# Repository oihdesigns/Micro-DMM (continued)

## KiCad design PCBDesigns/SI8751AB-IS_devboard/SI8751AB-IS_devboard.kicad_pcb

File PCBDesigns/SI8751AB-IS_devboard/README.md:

# Si8751 AC/DC development board — revision C

KiCad 10 bench prototype targeting **120 V RMS AC / 170 V DC, less than 1 A**, initially with resistive loads. Two SI8751AB-IS drivers operate back-to-back STP12N60M2 MOSFETs. **AMC3330DWER** measures switched voltage with integrated isolated power; **ACS725LLCTR-05AB-T** measures bidirectional load current. The entire board uses one regulated 3.3 V input. All resistors and capacitors are **0805**. The board is two layers, 110 × 90 mm, for 1.6 mm FR-4 and 35 µm copper.

Open `SI8751AB-IS_devboard.kicad_pro`. Reload schematic and board if an earlier revision is still open. Local symbols and footprints, a schematic PDF, BOM, and validation reports/previews are included. Prototype Gerbers and drills are in `fabrication/revC/`. `revision_B_before_3V3_sensor.zip` preserves revision B; the earlier revision A backup is also retained. The inventory workbook was read without modification; existing project preferences were preserved.

## Changes from revision B

- Replaced ACS712-05B with **ACS725LLCTR-05AB-T**, powered from +3V3.
- Removed the 5 V net. J1-7 is **NC**, preserving all other revision B header pin numbers.
- Removed R15/R16, the 2:1 current-output divider. J1-8 now receives the sensor output directly.
- C17 remains 100 nF; the ACS725 internal filter resistance gives approximately 884 Hz bandwidth. C18 is a direct 1 nF output load.
- Current conversion at nominal supply is now **I = (Vout − 1.65 V) / 0.264 V/A**.
- All passives remain 0805. The ACS725 was not found in the supplied purchase history and is a new procurement item.

## Earlier changes: revision A to B

- Added ACS712-05B between Q2 drain and J3 line. Positive current flows toward the load.
- Replaced AMC0330R with AMC3330. Removed SCT01F03S05, TPS70933 and the converter slot. U3/U4 and C9/C10 references are retired.
- Expanded J1 from 5 to 10 pins. **Pin 5 changed from ground to OUTN.** Voltage-interface firmware scaling also changed.
- Added regulated 5 V input, current filtering, 2:1 current-output attenuation, and AMC diagnostic output.
- Changed voltage divider to stocked 1 MΩ / 15 kΩ parts and EN pull-downs to stocked 75 kΩ parts.
- Corrected plated-pad solder-mask serialization in the generator; both mask openings are verified in the saved board.

## Connections

| Pin | Function |
|---|---|
| J1-1 | Regulated +3.3 V input; provide at least 100 mA capacity |
| J1-2 | Logic ground |
| J1-3 | EN, 3.3 V active high; both MOSFETs commanded together |
| J1-4 | VOUT_P, AMC positive differential output |
| J1-5 | VOUT_N, AMC negative differential output; **not ground** |
| J1-6 | Logic ground |
| J1-7 | NC, no connection; formerly the 5 V input in revision B |
| J1-8 | IOUT_ADC, direct ACS725 output referenced to logic ground |
| J1-9 | DIAG_N, AMC status, 10 kΩ pull-up to 3.3 V; LOW means invalid measurement |
| J1-10 | Logic ground |
| J2-1 / J2-2 | Source line / source return |
| J3-1 / J3-2 | Switched line / load return |

The regulated 3.3 V supply returns to GND_LOGIC, which must remain separate from GND_LOAD_RETURN and SOURCE_FLOAT. The ACS725 requires 3.0–3.6 V; do not power the board from 5 V. Power the host ADC with the board to avoid back-powering an unpowered ADC through the current output. J1-7 is unused; supply power at J1-1.

J2/J3 are Wuerth **691311400102**, 7.62 mm headers. Two **691351400002** cable plugs are additional assembly items outside the fitted PCB BOM. [Wuerth mating series](https://www.we-online.com/en/components/products/TBL_7_62_3514_VERTICAL_69135140000X).

## Switching circuit

```text
J2 LINE -- D Q1 S -- SOURCE_FLOAT -- S Q2 D -- ACS725 IP+ to IP- -- J3 LINE
             G1                         G2
             |                          |
          U1 GATE                    U2 GATE
          U1 SOURCE ---- SOURCE_FLOAT --- U2 SOURCE
J2 RETURN ---------------- GND_LOAD_RETURN -------------------- J3 RETURN
```

Opposing body diodes block either polarity when both gates are off. Driver gate outputs are separate. R1/R3 are 100 Ω input resistors, R2/R4 are 75 kΩ default-off pull-downs, and R5/R6 set TT to 10 kΩ. C3/C4 are 10 pF, 1 kV C0G drain-to-MCAP1 capacitors; MCAP2 is unused. A conventional gate/source bleed resistor would overload the weak generated gate supply and is omitted. [Skyworks datasheet](https://www.skyworksinc.com/-/media/SkyWorks/SL/documents/public/data-sheets/Si8751-2.pdf).

Q1/Q2 are 600 V STP12N60M2, TO-220, pins 1=G, 2=D, 3=S. Tabs are live drains at different potentials; do not attach both directly to one conductive heatsink. At 1 A and 0.45 Ω per MOSFET, combined conduction loss is about 0.9 W at the specified 10 V gate drive. Actual VGS, transition time and dissipation need measurement because driver output is load dependent. Begin at no more than one full on/off cycle per second. [ST part information](https://www.st.com/en/power-transistors/stp12n60m2.html).

## Voltage measurement

U5 receives 3.3 V on its logic side and generates isolated power internally. Its high-side reference connects to load return. OUTP/OUTN have differential gain 2 and need a differential ADC or external difference amplifier. This is not the old ratiometric output. Keep ADC wiring short: direct capacitive load limits are 500 pF per output to ground or 250 pF differential. The ADC must accept approximately 1.44 V output common mode. [TI AMC3330 datasheet](https://www.ti.com/lit/ds/symlink/amc3330.pdf).

R10–R12 are 1 MΩ each; R13 is 15 kΩ, all 0.1%. C14 is 1 nF. Nominal conversion:

```text
divider = (3,000,000 + 15,000) / 15,000 = 201
Vrail = 100.5 × (VOUT_P − VOUT_N)
```

| Calculated quantity | Nominal value |
|---|---:|
| Sense input at 120 V RMS sine | 0.8443 V peak |
| Sense input at 132 V RMS sine (+10% check) | 0.9288 V peak |
| Sense input at 170 V DC | 0.8458 V |
| Divider range for ±1 V linear AMC input | ±201 V instantaneous |
| Each top resistor at 132 V RMS | 61.92 V peak, 1.917 mW average |
| Divider current at 120 V RMS | 39.80 µA RMS |
| Divider / C14 pole | 10.66 kHz |

The 132 V calculation is a margin check, not a higher operating rating. RG2012 top resistors have a 150 V limiting element rating and 0.125 W regular power rating. Three parts share voltage; do not replace them with one 0805. [Susumu RG specification](https://www.susumu.co.jp/common/pdf/e_all.pdf).

C5/C6/C19 bypass DCDC_OUT/HLDO_IN; C7/C8 bypass HLDO_OUT; C11/C12 bypass VDD; C13 bypasses DCDC_IN/LDO_OUT. Use low-ESR ceramics with adequate effective capacitance under DC bias. No external LDO load or ferrite beads are fitted. EMI performance remains unqualified.

DIAG_N LOW invalidates measurements. Startup, loss of power or a zero reading does not establish that the rail is safe to touch. Calibrate zero/gain. For RMS, square calibrated instantaneous samples, average over complete cycles, then take the square root. Subtract the mean only for AC-only RMS.

## Current measurement

U6 is ACS725LLCTR-05AB-T, a 3.3 V, ±5 A bidirectional Hall sensor. Its analog output connects directly to J1-8 with no attenuation. At nominal 3.3 V supply:

```text
IOUT_ADC = 1.65 V + 0.264 V/A × I
I = (IOUT_ADC − 1.65 V) / 0.264 V/A
```

At ±1 A DC, output is 1.386–1.914 V. At 1 A RMS sine it moves ±0.3734 V about zero-current level. Nominal ±5 A span is 0.33–2.97 V, while the board load target remains below 1 A. ADC signal sensitivity is approximately 2.85 times revision B's divided output.

C17=100 nF and the nominal internal 1.8 kΩ resistance give a pole near 884 Hz, approximately 0.23% attenuation and 3.9° phase lag at 60 Hz. C18=1 nF is a direct output load. Total output capacitance, including the cable and ADC, must remain at or below 10 nF; DC load resistance must be at least 4.7 kΩ. Keep the ADC connection short and qualify its sampling-settling behavior. [Allegro ACS725 datasheet](https://www.allegromicro.com/-/media/files/datasheets/acs725-datasheet.ashx).

Calibrate zero with no current and gain against a known current. The formula assumes nominal supply: both zero and sensitivity vary with supply and temperature, so calibration at the actual operating supply is preferred. Do not assume simple ideal ratiometric cancellation removes every gain error. Offset and noise remain significant below 1 A. Characterize or compensate the filter phase response before power-factor or real-power measurements. This circuit monitors current; it does not implement hardware overcurrent shutdown.

The sensor pin functions match the earlier SOIC-8 part: 1/2 IP+, 3/4 IP−, 5 ground, 6 FILTER, 7 output, 8 supply. It cannot be fitted to an unmodified revision B assembly powered at 5 V. Use revision C supply wiring, component population and firmware scaling.

## Inventory and assembly

`BOM_inventory.csv` records MPNs, workbook row numbers, historical quantities and unmatched parts. **28 of 37 fitted references match exact MPNs.** U5 has the stocked automotive alternative **AMC3330QDWERQ1**: its DWE footprint, pin functions, integrated power and gain suit this design. Use its separate error/temperature specifications when qualifying that assembly. [TI automotive variant](https://www.ti.com/lit/ds/symlink/amc3330-q1.pdf).

Source: `C:\Users\Nick\Dropbox (Personal)\AvaliableParts\Combined_parts_DigiKey_and_Mouser.xlsx`, sheet `Combined parts`. Quantities describe purchase history, not verified remaining stock; repeated references consume shared stock.

| Items not found as exact inventory matches | Needed per board |
|---|---:|
| STP12N60M2 | 2 |
| ACS725LLCTR-05AB-T | 1 |
| C0805C100JDGACTU, 10 pF / 1 kV C0G | 2 |
| 691311400102 terminal header | 2 |
| 1×10, 2.54 mm vertical control header | 1 |
| AMC3330DWER, if stocked Q1 alternative is not used | 1 |

Cable plugs, an external fuse/holder and insulating mounting hardware are additional. Stocked 20–50 V MOSFETs are unsuitable for this voltage target.

## Layout and validation

Load-current traces are 0.8–1.0 mm wide; signal branches are 0.3 mm. High-voltage nodes use 0.8 mm copper clearance, the floating gate domain 0.3 mm, and logic-to-field copper 2.5 mm. There is no converter exception or slot. ACS IP+ and IP− are internally joined through a milliohm conductor, so mutual clearance is 0.3 mm; this exception never applies across its isolation barrier. TO-220 pads retain 1.1 mm drills with 1.65 mm copper width, giving 0.89 mm adjacent clearance. Four 3.2 mm mounting holes are included.

See `validation/revC_erc.rpt` and `validation/revC_drc.rpt` for ERC, DRC and schematic/PCB parity. Schematic, copper plot and board render are visually reviewed. These checks establish CAD consistency, not hardware performance or mains certification.

The entire board has **not** been certified for mains service. Use an appropriately isolated, current-limited bench source and an external fuse no greater than 1 A, rated for the actual AC/DC source and prospective fault current. Inductive/capacitive loads, inrush, surges, fault clearing, thermal limits and EMC remain unqualified. Terminals and MOSFET tabs are hazardous when energized.

Begin with no switched source: inspect assembly, check separation of all three ground domains, then apply regulated 3.3 V with a current limit. Check DIAG_N, voltage-output difference near zero, and current output near 1.65 V. Test switching and sensing first using current-limited low-voltage DC with a resistive load. Measure both VGS values and temperatures before increasing voltage. Calibrate voltage/current and evaluate AC response using isolated differential instrumentation. Never connect an earth-referenced scope ground to a live field node.

## Rebuilding

`build_design.py` writes schematic/metadata; `build_pcb.py` places/routes using KiCad Python and NumPy; `make_rules.py` creates rules; `match_bom.py` adds inventory matches using openpyxl. Run ERC/DRC after regeneration. Generators replace CAD contents: preserve manual edits before rerunning. Existing project preferences are preserved.

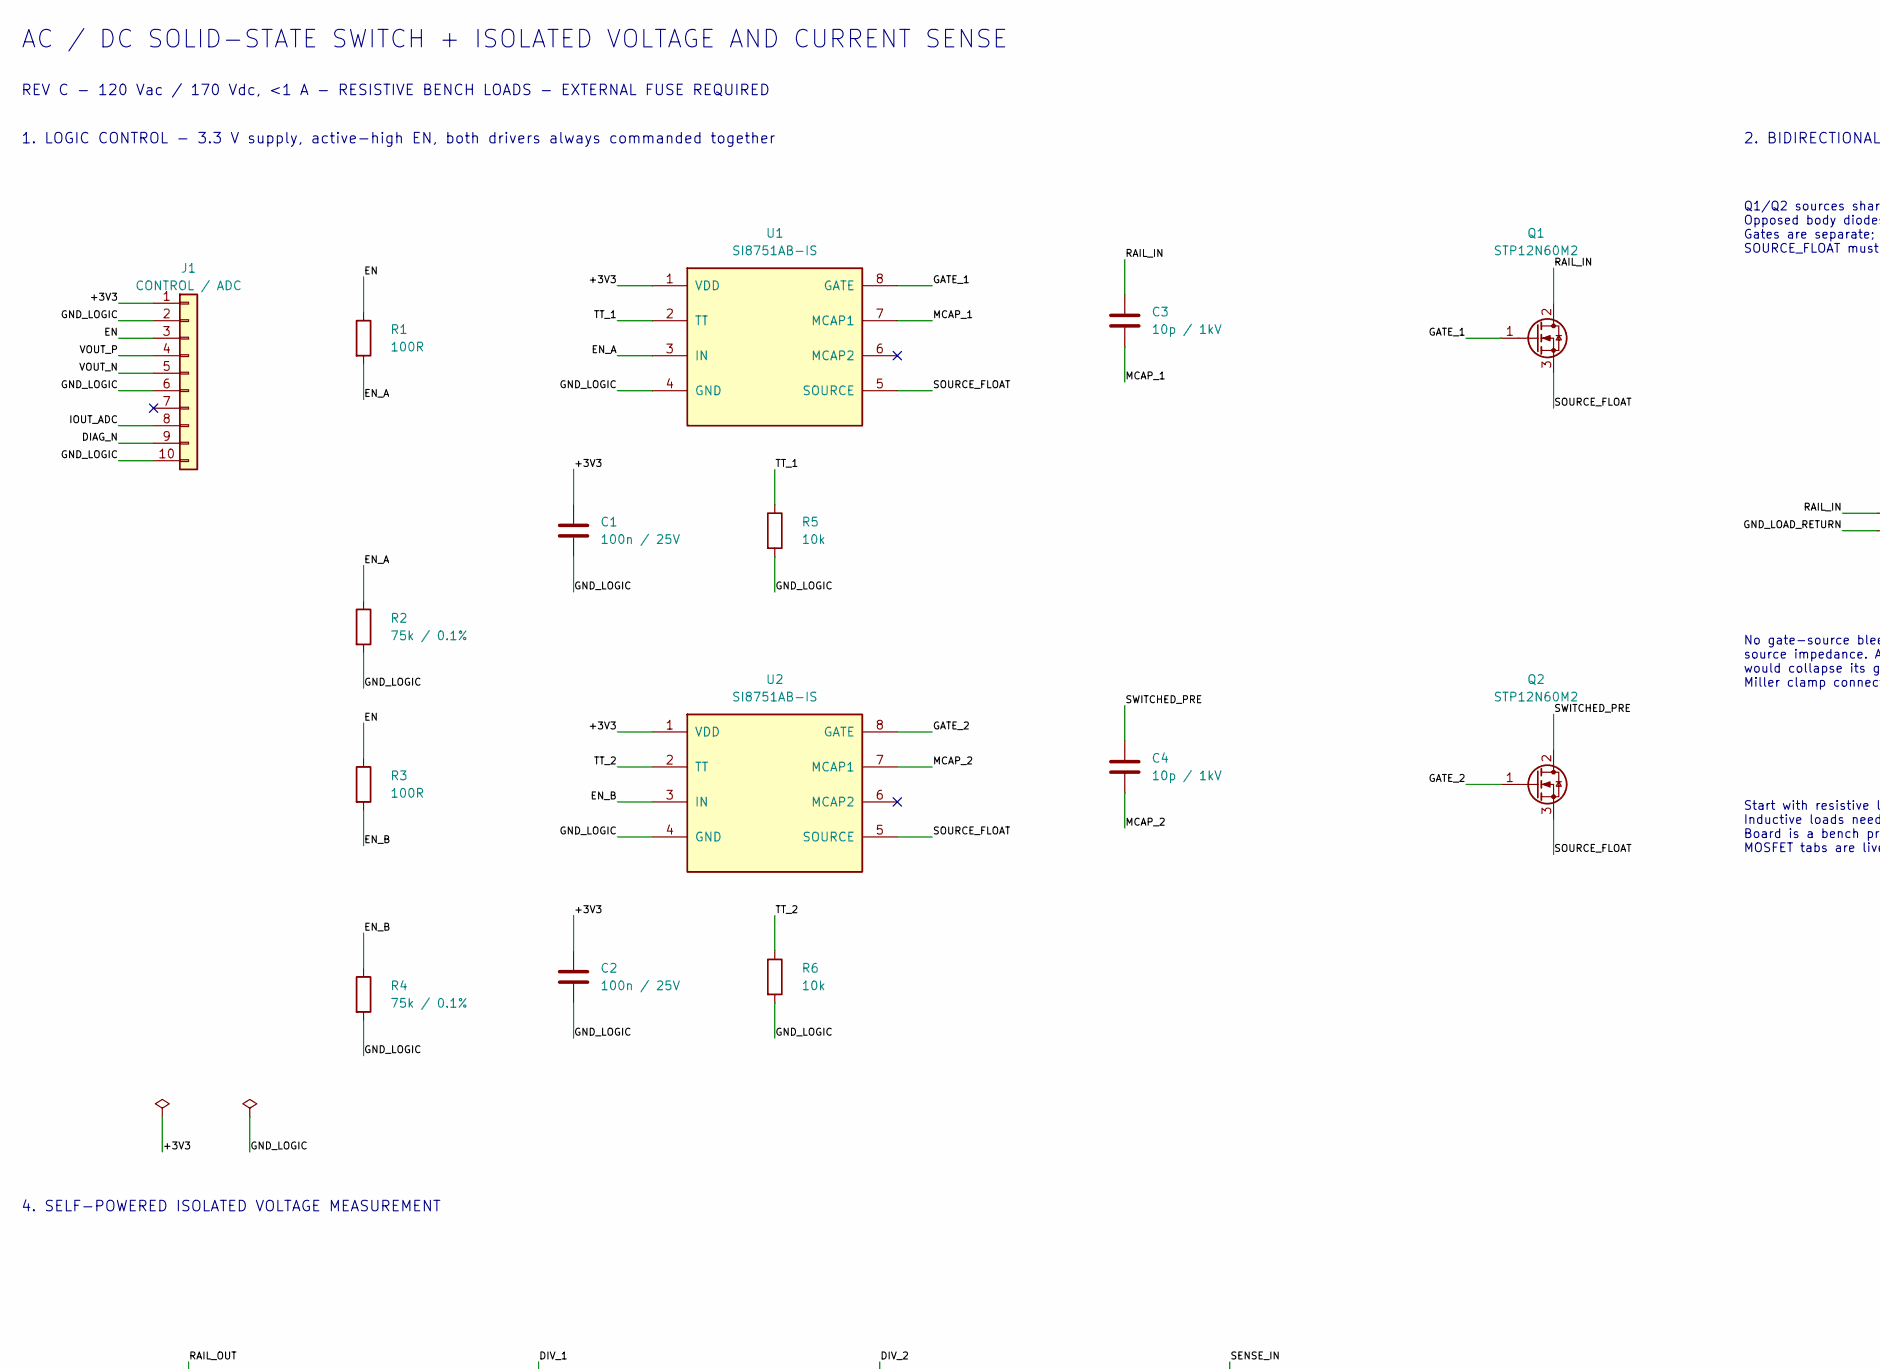
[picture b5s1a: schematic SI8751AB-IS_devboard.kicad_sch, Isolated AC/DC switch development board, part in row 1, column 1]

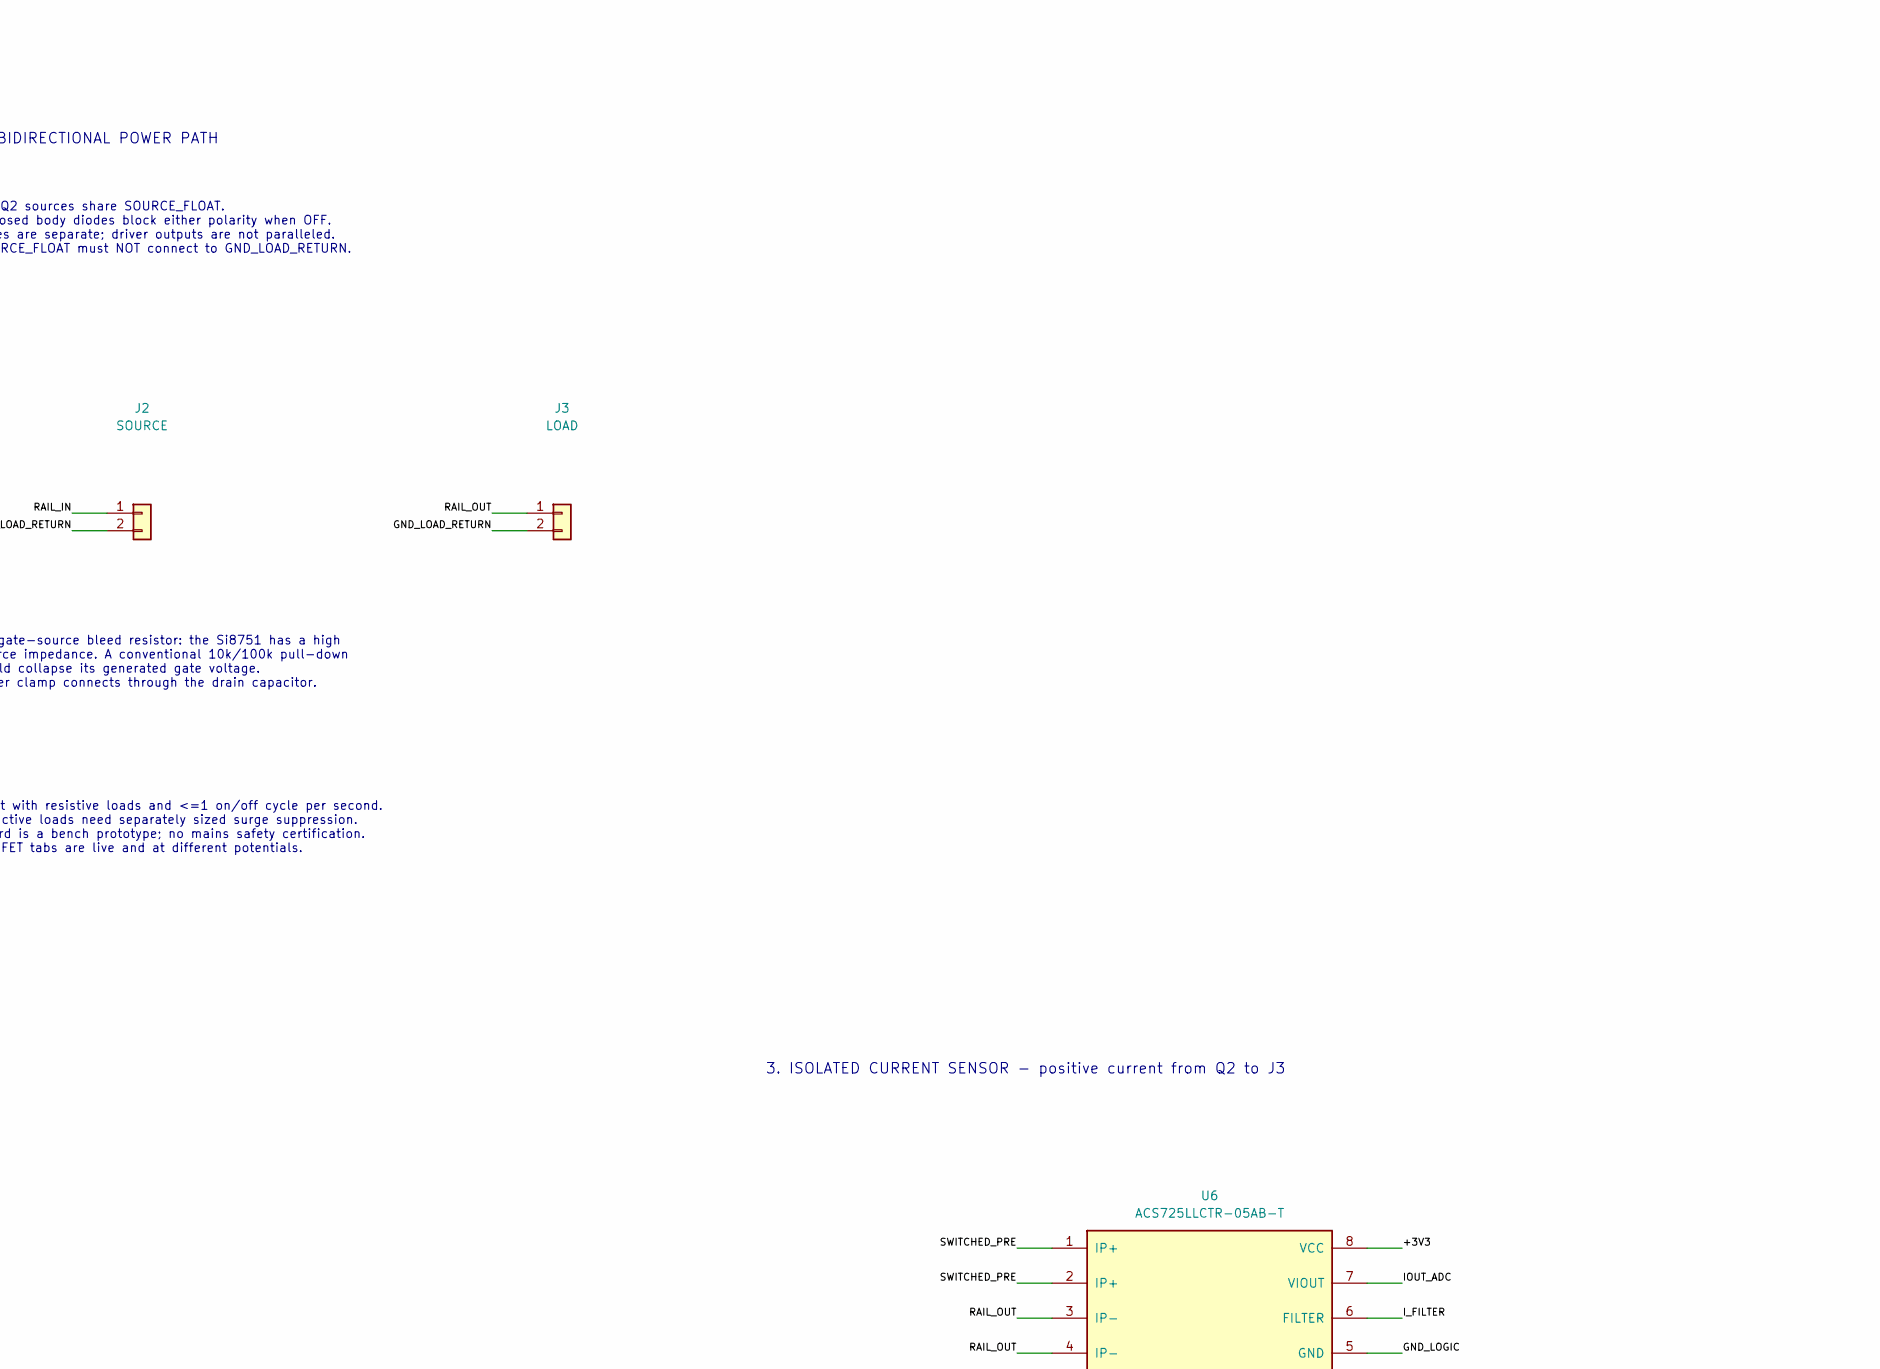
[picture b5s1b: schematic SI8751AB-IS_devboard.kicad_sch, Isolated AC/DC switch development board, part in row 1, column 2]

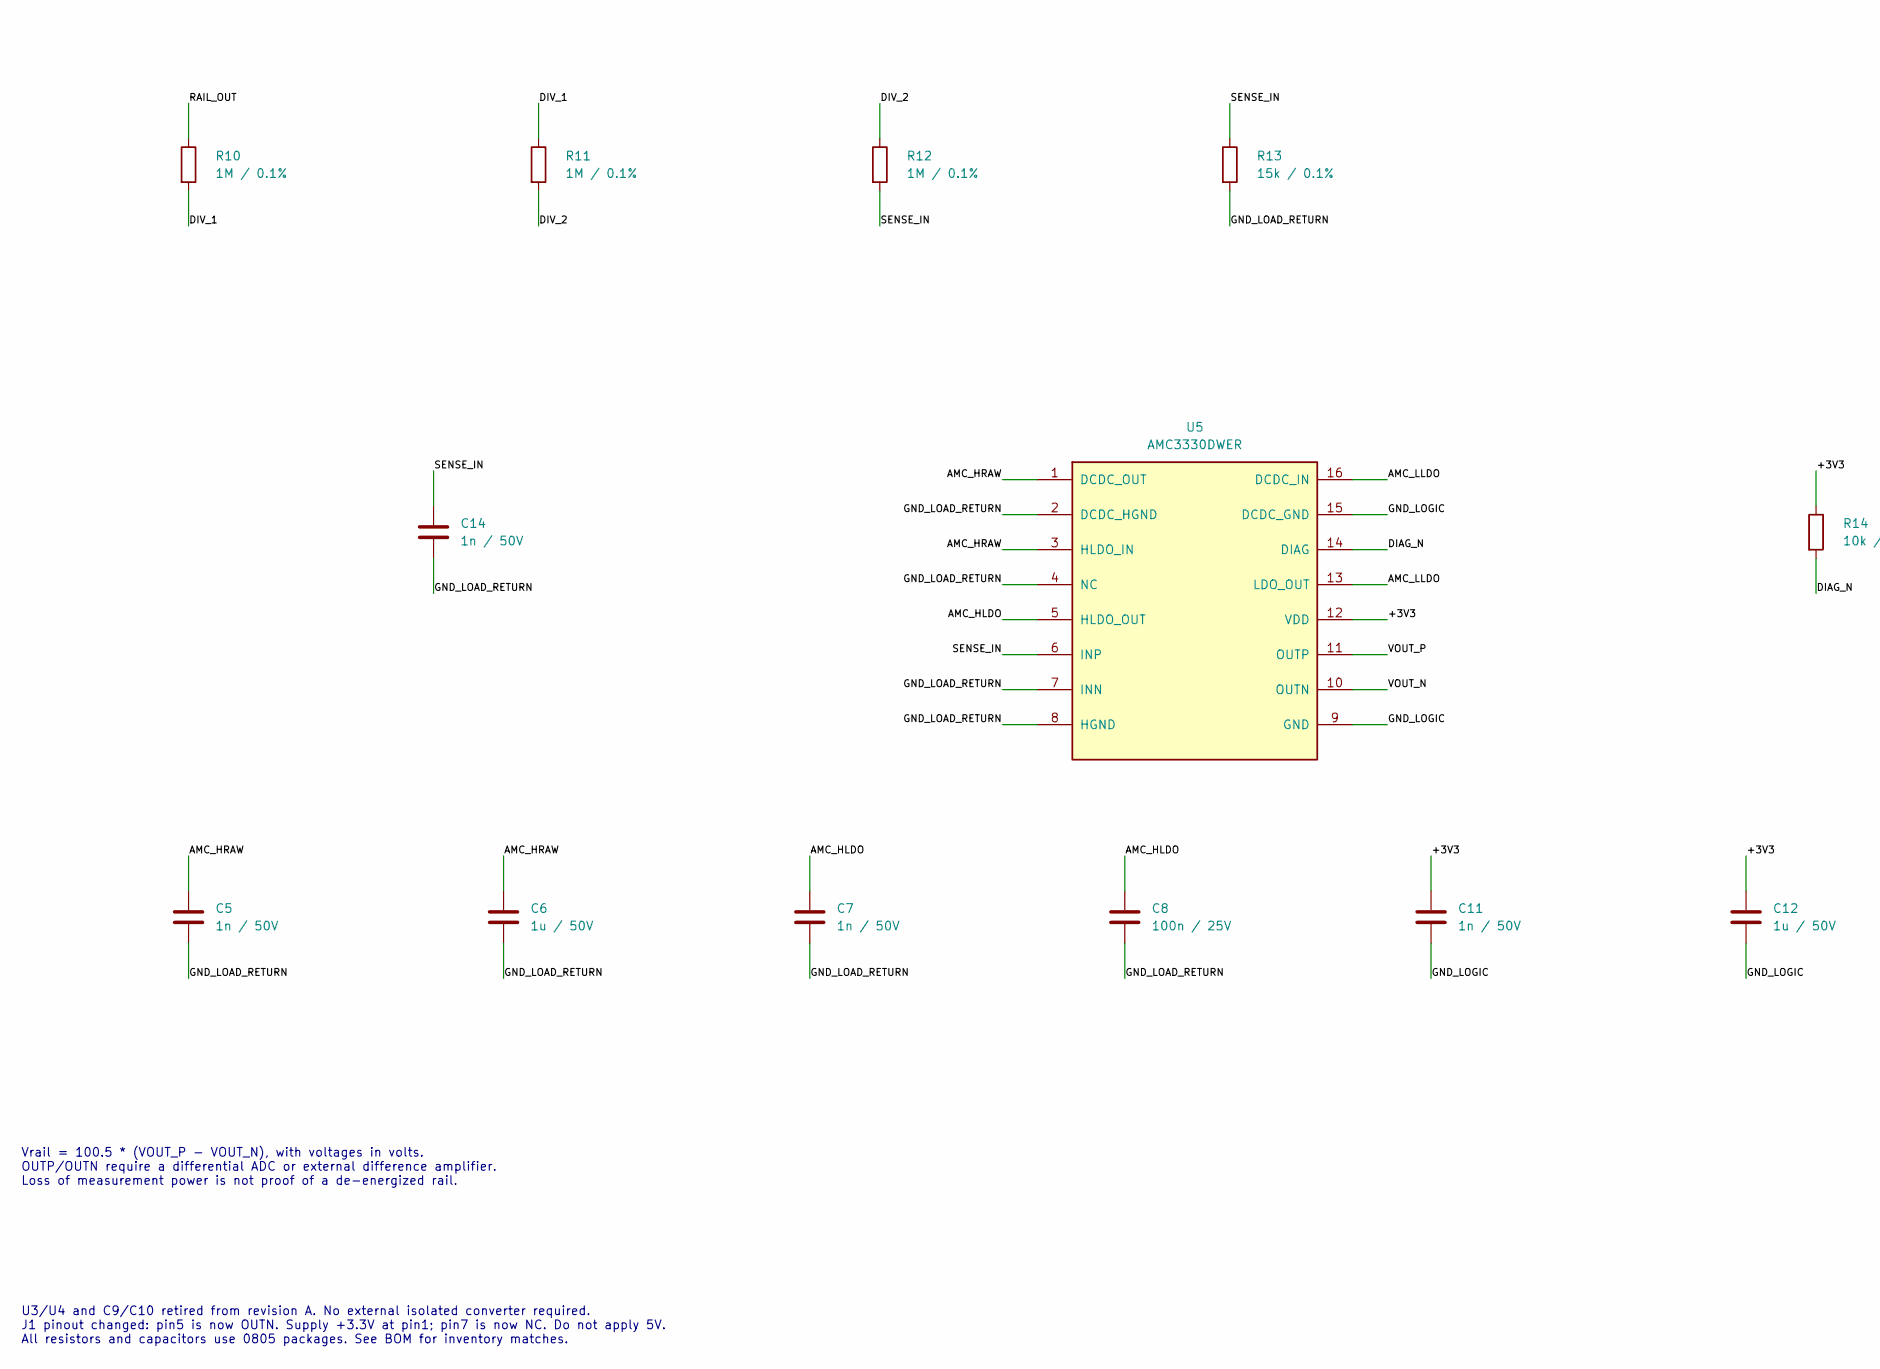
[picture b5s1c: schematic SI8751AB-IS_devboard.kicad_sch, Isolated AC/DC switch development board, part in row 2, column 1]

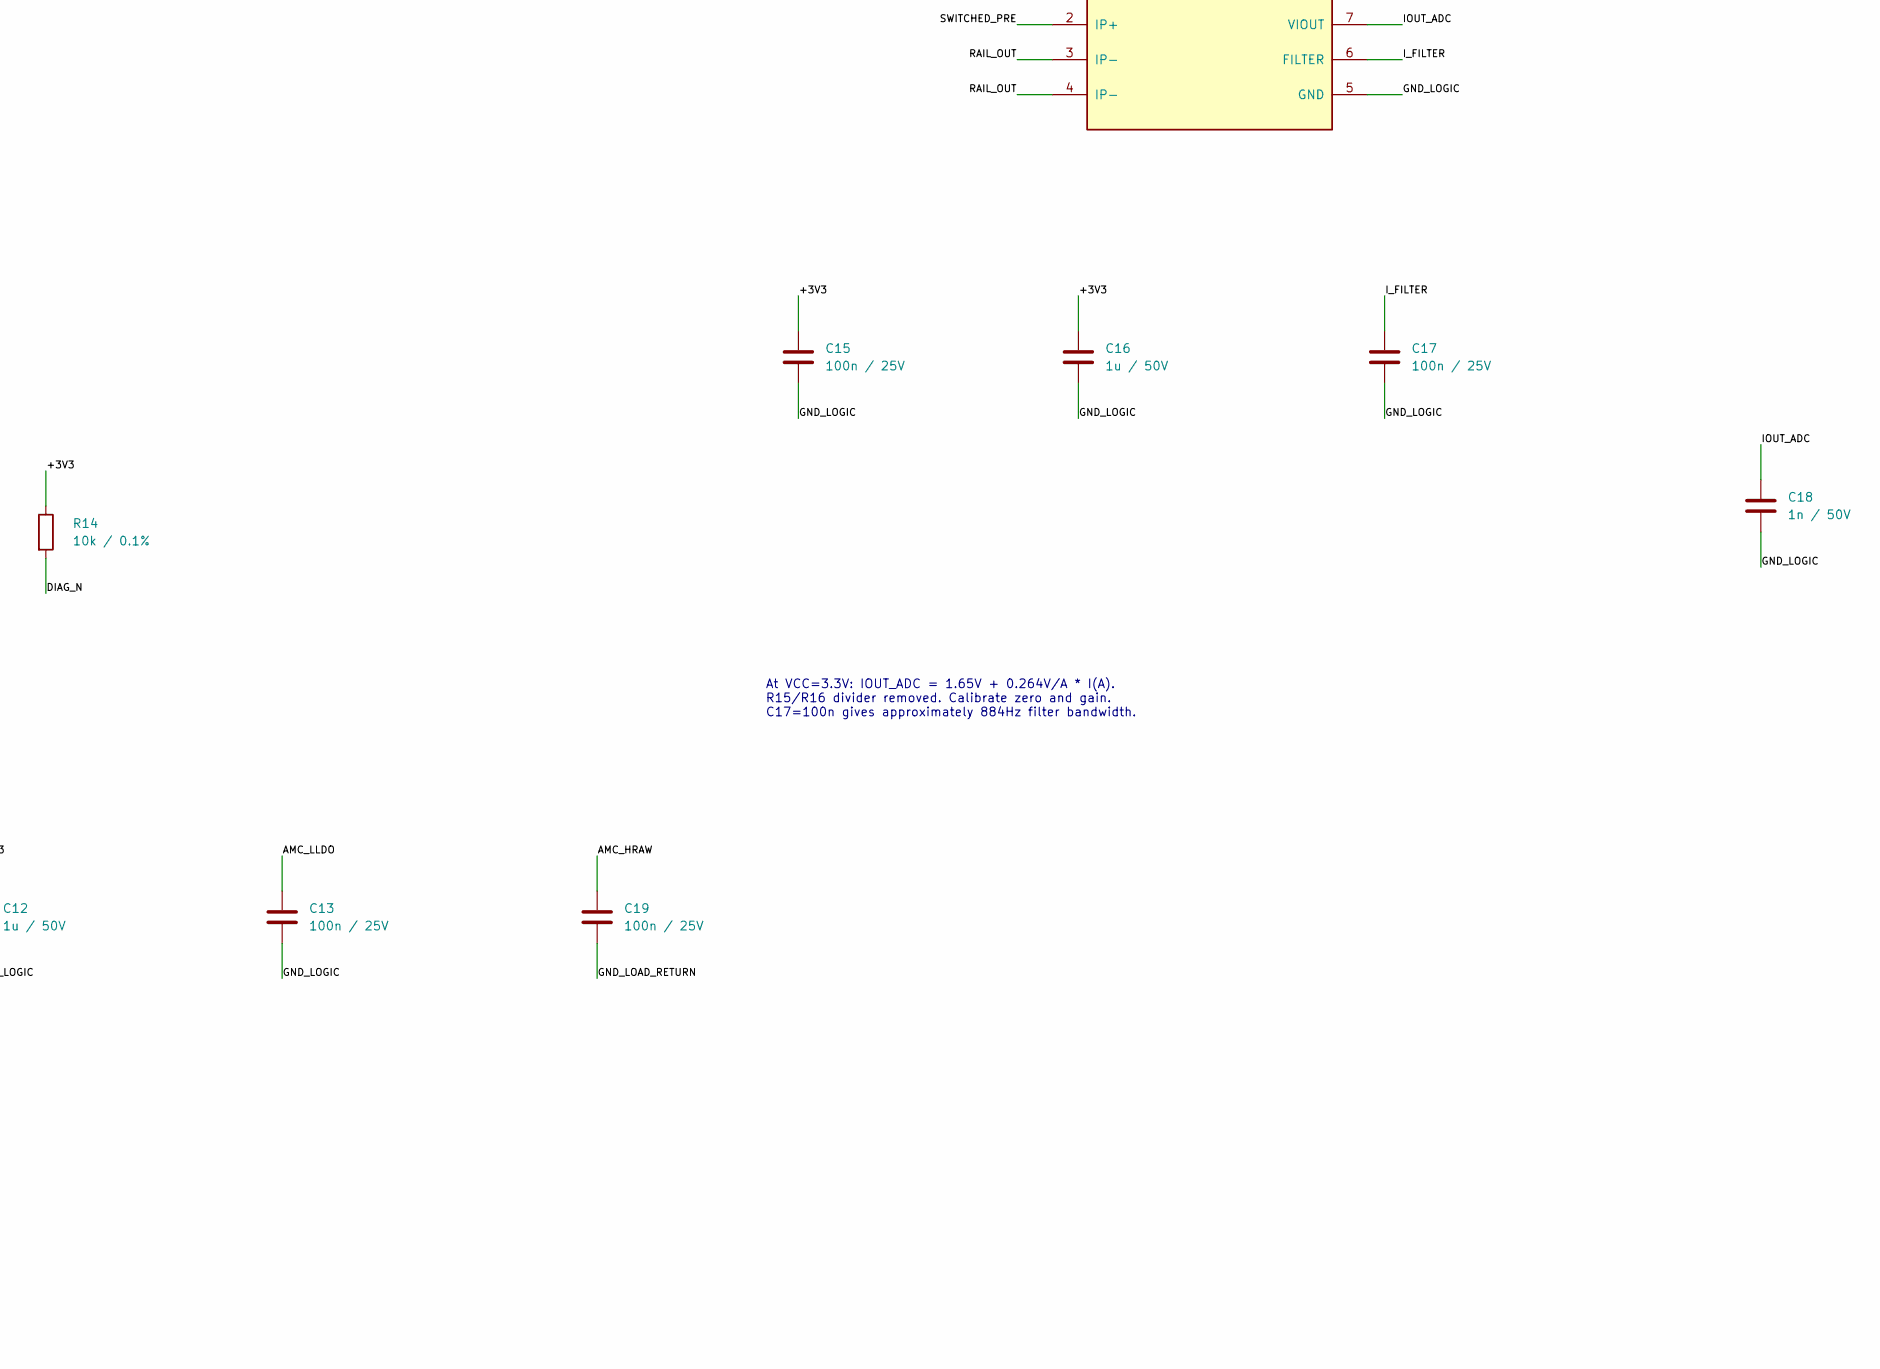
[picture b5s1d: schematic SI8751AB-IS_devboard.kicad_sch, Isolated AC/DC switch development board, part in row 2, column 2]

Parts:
C1, C2, C8, C13, C15, C17, C19: 100n / 25V; C_0805_2012Metric
C3, C4: 10p / 1kV; C_0805_2012Metric
C5, C7, C11, C14, C18: 1n / 50V; C_0805_2012Metric
C6, C12, C16: 1u / 50V; C_0805_2012Metric
J1: CONTROL / ADC; PinHeader_1x10_P2.54mm_Vertical
J2: SOURCE; Wuerth_691311400102_P7.62mm
J3: LOAD; Wuerth_691311400102_P7.62mm
Q1, Q2: STP12N60M2; TO-220-3_Vertical
R1, R3: 100R; R_0805_2012Metric
R2, R4: 75k / 0.1%; R_0805_2012Metric
R5, R6: 10k; R_0805_2012Metric
R10, R11, R12: 1M / 0.1%; R_0805_2012Metric
R13: 15k / 0.1%; R_0805_2012Metric
R14: 10k / 0.1%; R_0805_2012Metric
U1, U2: SI8751AB-IS; SOIC-8_3.9x4.9mm_P1.27mm
U5: AMC3330DWER; SOIC-16W_7.5x10.3mm_P1.27mm
U6: ACS725LLCTR-05AB-T; SOIC-8_3.9x4.9mm_P1.27mm

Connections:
/+3V3: C1.1, C2.1, C11.1, C12.1, C15.1, C16.1, J1.1, R14.1, U1.1 (VDD), U2.1 (VDD), U5.12 (VDD), U6.8 (VCC)
/AMC_HLDO: C7.1, C8.1, U5.5 (HLDO_OUT)
/AMC_HRAW: C5.1, C6.1, C19.1, U5.1 (DCDC_OUT), U5.3 (HLDO_IN)
/AMC_LLDO: C13.1, U5.13 (LDO_OUT), U5.16 (DCDC_IN)
/DIAG_N: J1.9, R14.2, U5.14 (DIAG)
/DIV_1: R10.2, R11.1
/DIV_2: R11.2, R12.1
/EN: J1.3, R1.1, R3.1
/EN_A: R1.2, R2.1, U1.3 (IN)
/EN_B: R3.2, R4.1, U2.3 (IN)
/GATE_1: Q1.1 (G), U1.8 (GATE)
/GATE_2: Q2.1 (G), U2.8 (GATE)
/GND_LOAD_RETURN: C5.2, C6.2, C7.2, C8.2, C14.2, C19.2, J2.2, J3.2, R13.2, U5.2 (DCDC_HGND), U5.4 (NC), U5.7 (INN), U5.8 (HGND)
/GND_LOGIC: C1.2, C2.2, C11.2, C12.2, C13.2, C15.2, C16.2, C17.2, C18.2, J1.2, J1.6, J1.10, R2.2, R4.2, R5.2, R6.2, U1.4 (GND), U2.4 (GND), U5.9 (GND), U5.15 (DCDC_GND), U6.5 (GND)
/IOUT_ADC: C18.1, J1.8, U6.7 (VIOUT)
/I_FILTER: C17.1, U6.6 (FILTER)
/MCAP_1: C3.2, U1.7 (MCAP1)
/MCAP_2: C4.2, U2.7 (MCAP1)
/RAIL_IN: C3.1, J2.1, Q1.2 (D)
/RAIL_OUT: J3.1, R10.1, U6.3 (IP-), U6.4 (IP-)
/SENSE_IN: C14.1, R12.2, R13.1, U5.6 (INP)
/SOURCE_FLOAT: Q1.3 (S), Q2.3 (S), U1.5 (SOURCE), U2.5 (SOURCE)
/SWITCHED_PRE: C4.1, Q2.2 (D), U6.1 (IP+), U6.2 (IP+)
/TT_1: R5.1, U1.2 (TT)
/TT_2: R6.1, U2.2 (TT)
/VOUT_N: J1.5, U5.10 (OUTN)
/VOUT_P: J1.4, U5.11 (OUTP)

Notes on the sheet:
AC / DC SOLID-STATE SWITCH + ISOLATED VOLTAGE AND CURRENT SENSE
REV C - 120 Vac / 170 Vdc, <1 A - RESISTIVE BENCH LOADS - EXTERNAL FUSE REQUIRED
1. LOGIC CONTROL - 3.3 V supply, active-high EN, both drivers always commanded together
2. BIDIRECTIONAL POWER PATH
Q1/Q2 sources share SOURCE_FLOAT. Opposed body diodes block either polarity when OFF. Gates are separate; driver outputs are not paralleled. SOURCE_FLOAT must NOT connect to GND_LOAD_RETURN.
No gate-source bleed resistor: the Si8751 has a high source impedance. A conventional 10k/100k pull-down would collapse its generated gate voltage. Miller clamp connects through the drain capacitor.
Start with resistive loads and <=1 on/off cycle per second. Inductive loads need separately sized surge suppression. Board is a bench prototype; no mains safety certification. MOSFET tabs are live and at different potentials.
3. ISOLATED CURRENT SENSOR - positive current from Q2 to J3
At VCC=3.3V: IOUT_ADC = 1.65V + 0.264V/A * I(A). R15/R16 divider removed. Calibrate zero and gain. C17=100n gives approximately 884Hz filter bandwidth.
4. SELF-POWERED ISOLATED VOLTAGE MEASUREMENT
Vrail = 100.5 * (VOUT_P - VOUT_N), with voltages in volts. OUTP/OUTN require a differential ADC or external difference amplifier. Loss of measurement power is not proof of a de-energized rail.
U3/U4 and C9/C10 retired from revision A. No external isolated converter required. J1 pinout changed: pin5 is now OUTN. Supply +3.3V at pin1; pin7 is now NC. Do not apply 5V. All resistors and capacitors use 0805 packages. See BOM for inventory matches.

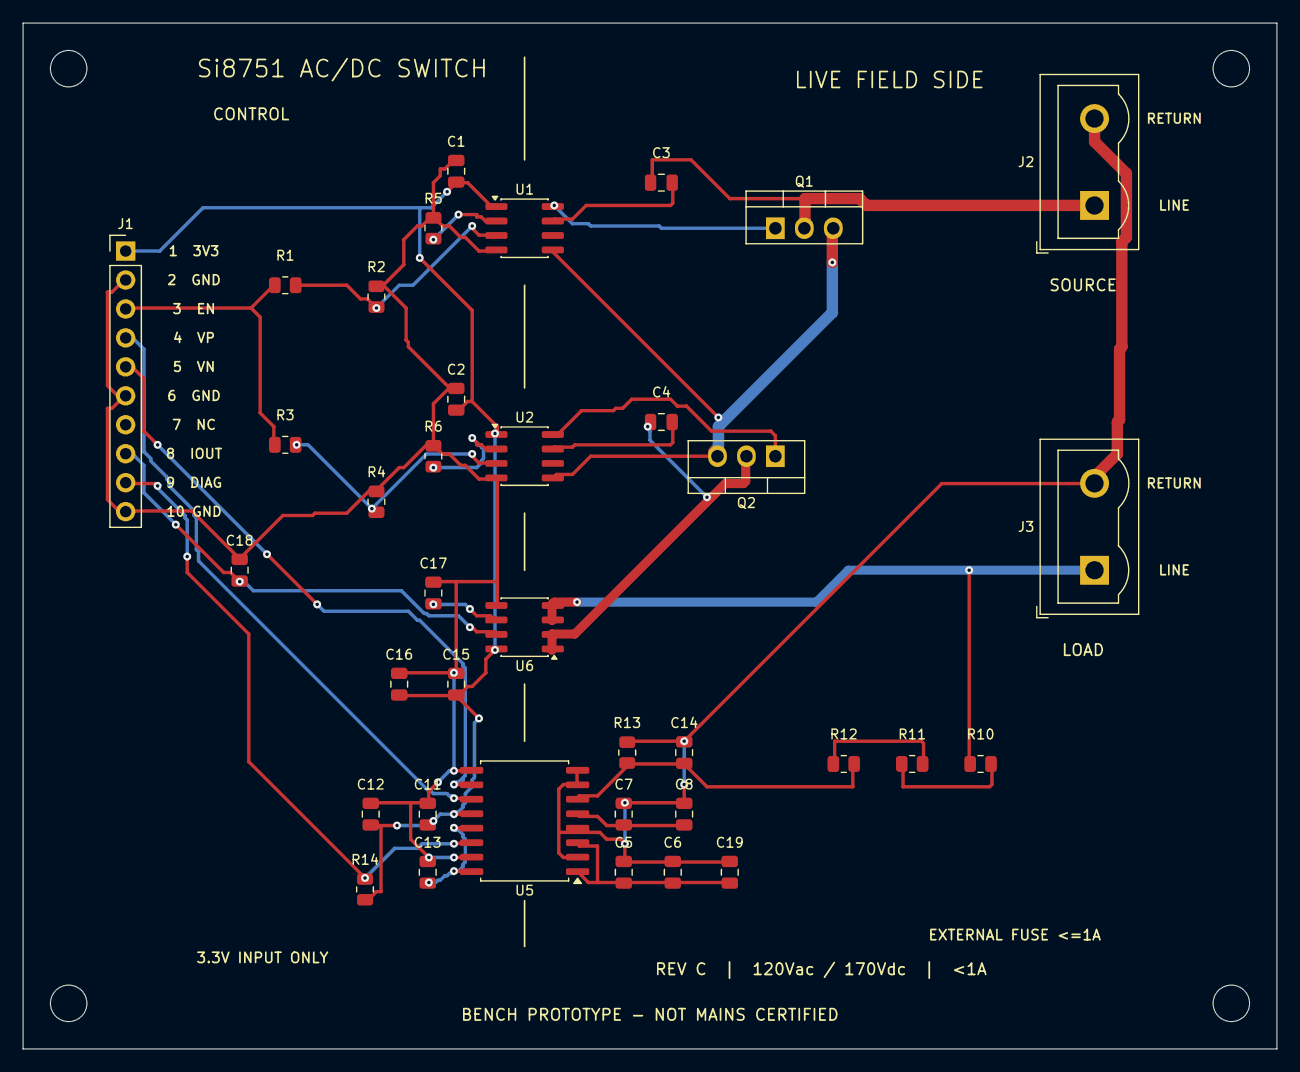
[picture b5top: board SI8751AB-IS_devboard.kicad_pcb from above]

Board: 2 copper layers, 110.0 x 90.0 mm, 41 parts (0 on the bottom side), 27 nets.

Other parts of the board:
H1, H2, H3, H4: MountingHole_3.2mm_M3

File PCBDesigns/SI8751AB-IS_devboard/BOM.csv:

reference,value,manufacturer_part_number,stocked_alternative,inventory_match,inventory_sheet_row,historical_quantity,footprint,purpose,datasheet
J1,CONTROL / ADC,Generic 1x10 2.54mm vertical header,,Not found in purchase history,,,Devboard:PinHeader_1x10_P2.54mm_Vertical,Rev C: 3.3V only; pin7 NC (formerly 5V); current output is no longer divided,
R1,100R,RNCF0805DTE100R,,Exact MPN,123,50,Devboard:R_0805_2012Metric,Series input damping,
R2,75k / 0.1%,ERA-6AEB753V,,Exact MPN,139,50,Devboard:R_0805_2012Metric,Default OFF; stocked ERA-6AEB753V,
R3,100R,RNCF0805DTE100R,,Exact MPN,123,50,Devboard:R_0805_2012Metric,Series input damping,
R4,75k / 0.1%,ERA-6AEB753V,,Exact MPN,139,50,Devboard:R_0805_2012Metric,Default OFF; stocked ERA-6AEB753V,
U1,SI8751AB-IS,SI8751AB-IS,,Exact MPN,90,10,Devboard:SOIC-8_3.9x4.9mm_P1.27mm,One isolated gate driver per MOSFET,https://www.skyworksinc.com/-/media/SkyWorks/SL/documents/pu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
C1,100n / 25V,CL21B104KACNNNC,,Exact MPN,17,200,Devboard:C_0805_2012Metric,Place beside driver VDD / GND,
R5,10k,RN73H2ATTD1002B25,,Exact MPN,121,50,Devboard:R_0805_2012Metric,TT=10k: 9V minimum unloaded gate output; qualify actual VGS under load,
C3,10p / 1kV,C0805C100JDGACTU,,Not found in purchase history,,,Devboard:C_0805_2012Metric,0805 C0G 1kV; qualify dV/dt <=600V/us for 6mA MCAP limit,
Q1,STP12N60M2,STP12N60M2,,Not found in purchase history,,,Devboard:TO-220-3_Vertical,600V NMOS; RDSon specified at 10V; qualify VGS and dissipation on prototype,https://www.st.com/resource/en/datasheet/stp12n60m2.pdf
U2,SI8751AB-IS,SI8751AB-IS,,Exact MPN,90,10,Devboard:SOIC-8_3.9x4.9mm_P1.27mm,One isolated gate driver per MOSFET,https://www.skyworksinc.com/-/media/SkyWorks/SL/documents/pu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
C2,100n / 25V,CL21B104KACNNNC,,Exact MPN,17,200,Devboard:C_0805_2012Metric,Place beside driver VDD / GND,
R6,10k,RN73H2ATTD1002B25,,Exact MPN,121,50,Devboard:R_0805_2012Metric,TT=10k: 9V minimum unloaded gate output; qualify actual VGS under load,
C4,10p / 1kV,C0805C100JDGACTU,,Not found in purchase history,,,Devboard:C_0805_2012Metric,0805 C0G 1kV; qualify dV/dt <=600V/us for 6mA MCAP limit,
Q2,STP12N60M2,STP12N60M2,,Not found in purchase history,,,Devboard:TO-220-3_Vertical,600V NMOS; RDSon specified at 10V; qualify VGS and dissipation on prototype,https://www.st.com/resource/en/datasheet/stp12n60m2.pdf
J2,SOURCE,691311400102,,Not found in purchase history,,,Devboard:Wuerth_691311400102_P7.62mm,"Wuerth 691311400102, 7.62mm; feed through external appropriately rated <=1A fuse",
J3,LOAD,691311400102,,Not found in purchase history,,,Devboard:Wuerth_691311400102_P7.62mm,Switched line / unswitched return; resistive loads initially,
U6,ACS725LLCTR-05AB-T,ACS725LLCTR-05AB-T,,Not found in purchase history,,,Devboard:SOIC-8_3.9x4.9mm_P1.27mm,3.3V supply; 264mV/A nominal; zero-current output VCC/2; isolated series current conductor,https://www.allegromicro.com/-/media/files/datasheets/acs725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
C15,100n / 25V,CL21B104KACNNNC,,Exact MPN,17,200,Devboard:C_0805_2012Metric,ACS VCC bypass,
C16,1u / 50V,CL21B105KBFNNNE,,Exact MPN,15,100,Devboard:C_0805_2012Metric,ACS VCC bulk,
C17,100n / 25V,CL21B104KACNNNC,,Exact MPN,17,200,Devboard:C_0805_2012Metric,Internal 1.8k plus 100n: approximately 884Hz pole,
C18,1n / 50V,C0805C102K5HACAUTO,,Exact MPN,14,120,Devboard:C_0805_2012Metric,Direct output load; total output capacitance <=10nF and DC load >=4.7k; qualify host ADC settling,
R10,1M / 0.1%,RG2012P-105-B-T5,,Exact MPN,120,50,Devboard:R_0805_2012Metric,"RG2012P-105-B-T5; 0805, 150V limiting element voltage, 0.125W",
R11,1M / 0.1%,RG2012P-105-B-T5,,Exact MPN,120,50,Devboard:R_0805_2012Metric,"RG2012P-105-B-T5; 0805, 150V limiting element voltage, 0.125W",
R12,1M / 0.1%,RG2012P-105-B-T5,,Exact MPN,120,50,Devboard:R_0805_2012Metric,"RG2012P-105-B-T5; 0805, 150V limiting element voltage, 0.125W",
R13,15k / 0.1%,RG2012P-153-B-T5,,Exact MPN,124,50,Devboard:R_0805_2012Metric,RG2012P-153-B-T5; divider factor 201; input 0.8443Vpk at 120Vac,
U5,AMC3330DWER,AMC3330DWER,AMC3330QDWERQ1,Compatible automotive variant; see README,92,10,Devboard:SOIC-16W_7.5x10.3mm_P1.27mm,Integrated isolated DC/DC; fixed differential gain 2; stocked AMC3330QDWERQ1 is an assembly alternative,https://www.ti.com/lit/ds/symlink/amc3330.pdf
C5,1n / 50V,C0805C102K5HACAUTO,,Exact MPN,14,120,Devboard:C_0805_2012Metric,DCDC_OUT pin1 / DCDC_HGND pin2 HF bypass,
C6,1u / 50V,CL21B105KBFNNNE,,Exact MPN,15,100,Devboard:C_0805_2012Metric,DCDC_OUT bulk; 1u effective target,
C19,100n / 25V,CL21B104KACNNNC,,Exact MPN,17,200,Devboard:C_0805_2012Metric,HLDO_IN local bypass at pin3; no ferrite beads fitted,
C7,1n / 50V,C0805C102K5HACAUTO,,Exact MPN,14,120,Devboard:C_0805_2012Metric,HLDO_OUT HF bypass,
C8,100n / 25V,CL21B104KACNNNC,,Exact MPN,17,200,Devboard:C_0805_2012Metric,HLDO_OUT bypass; no external load,
C11,1n / 50V,C0805C102K5HACAUTO,,Exact MPN,14,120,Devboard:C_0805_2012Metric,VDD HF bypass,
C12,1u / 50V,CL21B105KBFNNNE,,Exact MPN,15,100,Devboard:C_0805_2012Metric,VDD bulk; 1u effective target,
C13,100n / 25V,CL21B104KACNNNC,,Exact MPN,17,200,Devboard:C_0805_2012Metric,DCDC_IN pin16 to DCDC_GND pin15; no external load,
C14,1n / 50V,C0805C102K5HACAUTO,,Exact MPN,14,120,Devboard:C_0805_2012Metric,Input filter: approximately 10.7kHz; return at AMC INN,
R14,10k / 0.1%,RN73H2ATTD1002B25,,Exact MPN,121,50,Devboard:R_0805_2012Metric,Active-low open-drain diagnostic pullup; LOW means invalid measurement,
